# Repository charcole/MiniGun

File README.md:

# MiniGun - A mini super gun (JAMMA on TV)

A device for playing JAMMA compatible arcade boards on a TV using Wii Classic Controllers

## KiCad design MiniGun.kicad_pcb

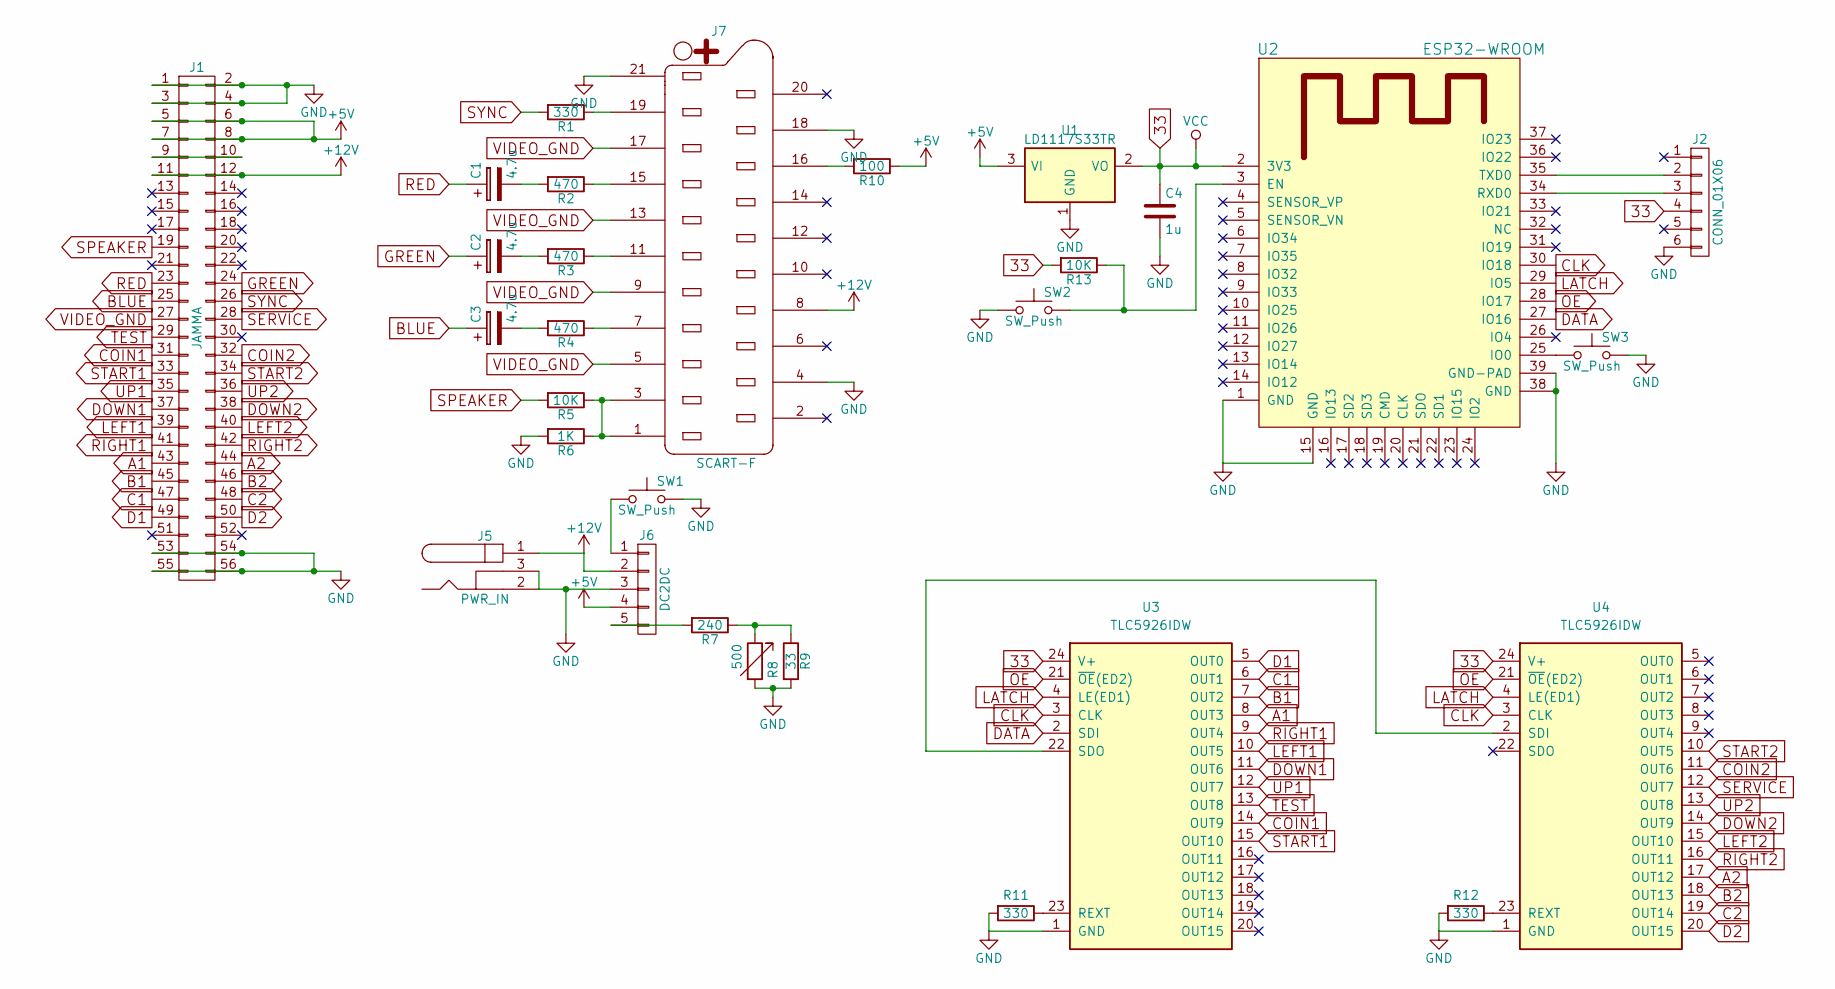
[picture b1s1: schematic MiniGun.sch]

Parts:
C1, C2, C3: 4.7u; C_1206_HandSoldering
C4: 1u; C_1206_HandSoldering
J1: JAMMA
J2: CONN_01X06; Pin_Header_Straight_1x06
J5: PWR_IN; BARREL_JACK
J6: DC2DC; NQR010A0X4Z
J7: SCART-F; SCART
R1, R11, R12: 330; R_1206_HandSoldering
R2, R3, R4: 470; R_1206_HandSoldering
R5, R13: 10K; R_1206_HandSoldering
R6: 1K; R_1206_HandSoldering
R7: 240; R_1206_HandSoldering
R8: 500; Potentiometer_Bourns_3296W_3-8Zoll_Inline_ScrewUp
R9: 33; R_1206_HandSoldering
R10: 100; R_1206_HandSoldering
SW1, SW2, SW3: SW_Push; SW_SPST_EVQPE1
U1: LD1117S33TR; SOT-223
U2: ESP32-WROOM
U3, U4: TLC5926IDW; SOIC-24W_7.5x15.4mm_Pitch1.27mm; MPN TLC5926IDW

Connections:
33: C4.1, J2.4, R13.2, U1.2 (VO), U2.2 (3V3), U3.24 (V+), U4.24 (V+)
+5V: J1.5, J1.6, J1.7, J1.8, J6.4, R10.1, U1.3 (VI)
+12V: J1.11, J1.12, J5.1, J6.2, J7.8
A1: J1.43, U3.8 (OUT3)
A2: J1.44, U4.17 (OUT12)
B1: J1.45, U3.7 (OUT2)
B2: J1.46, U4.18 (OUT13)
BLUE: C3.1, J1.25
C1: J1.47, U3.6 (OUT1)
C2: J1.48, U4.19 (OUT14)
CLK: U2.30 (IO18), U3.3 (CLK), U4.3 (CLK)
COIN1: J1.31, U3.14 (OUT9)
COIN2: J1.32, U4.11 (OUT6)
D1: J1.49, U3.5 (OUT0)
D2: J1.50, U4.20 (OUT15)
DATA: U2.27 (IO16), U3.2 (SDI)
DOWN1: J1.37, U3.11 (OUT6)
DOWN2: J1.38, U4.14 (OUT9)
GND: C4.2, J1.1, J1.2, J1.3, J1.4, J1.53, J1.54, J1.55, J1.56, J2.6, J5.2, J5.3, J6.3, J7.4, J7.18, J7.21, R6.2, R8.2, R9.2, R11.2, R12.2, SW1.2, SW2.1, SW3.2, U1.1 (GND), U2.1 (GND), U2.15 (GND), U2.38 (GND), U2.39 (GND-PAD), U3.1 (GND), U4.1 (GND)
GREEN: C2.1, J1.24
LATCH: U2.29 (IO5), U3.4 (LE(ED1)), U4.4 (LE(ED1))
LEFT1: J1.39, U3.10 (OUT5)
LEFT2: J1.40, U4.15 (OUT10)
unnamed: C1.2, R2.2
unnamed: C2.2, R3.2
unnamed: C3.2, R4.2
unnamed: J1.9, J1.10
unnamed: J2.2, U2.35 (TXD0)
unnamed: J2.3, U2.34 (RXD0)
unnamed: J6.1, SW1.1
unnamed: J6.5, R7.2
unnamed: J7.1, J7.3, R5.1, R6.1
unnamed: J7.7, R4.1
unnamed: J7.11, R3.1
unnamed: J7.15, R2.1
unnamed: J7.16, R10.2
unnamed: J7.19, R1.1
unnamed: R7.1, R8.1, R9.1
unnamed: R11.1, U3.23 (REXT)
unnamed: R12.1, U4.23 (REXT)
unnamed: R13.1, SW2.2, U2.3 (EN)
unnamed: SW3.1, U2.25 (IO0)
unnamed: U3.22 (SDO), U4.2 (SDI)
OE: U2.28 (IO17), U3.21 (~OE~(ED2)), U4.21 (~OE~(ED2))
RED: C1.1, J1.23
RIGHT1: J1.41, U3.9 (OUT4)
RIGHT2: J1.42, U4.16 (OUT11)
SERVICE: J1.28, U4.12 (OUT7)
SPEAKER: J1.19, R5.2
START1: J1.33, U3.15 (OUT10)
START2: J1.34, U4.10 (OUT5)
SYNC: J1.26, R1.2
TEST: J1.29, U3.13 (OUT8)
UP1: J1.35, U3.12 (OUT7)
UP2: J1.36, U4.13 (OUT8)
VIDEO_GND: J1.27, J7.5, J7.9, J7.13, J7.17

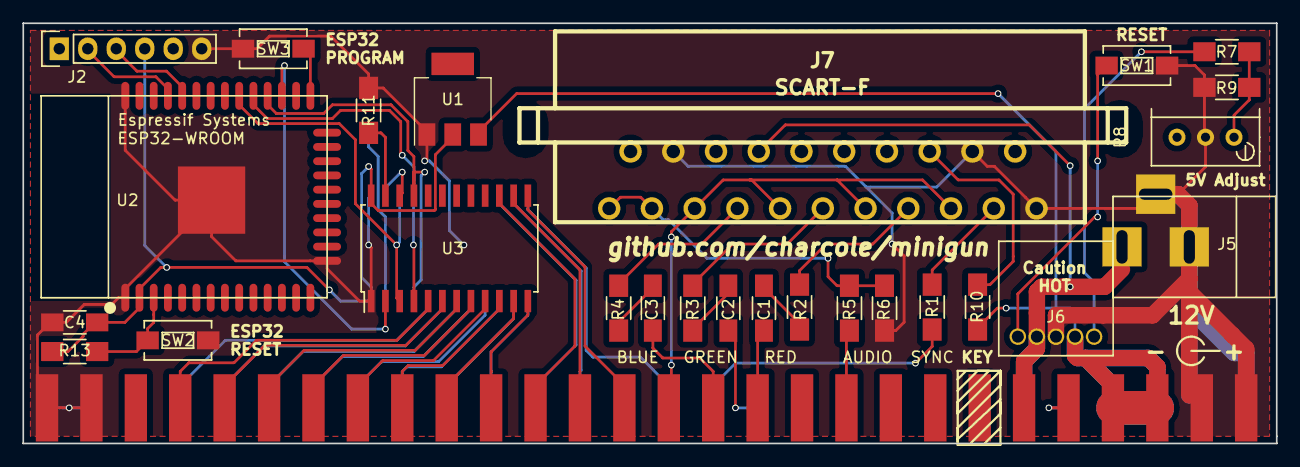
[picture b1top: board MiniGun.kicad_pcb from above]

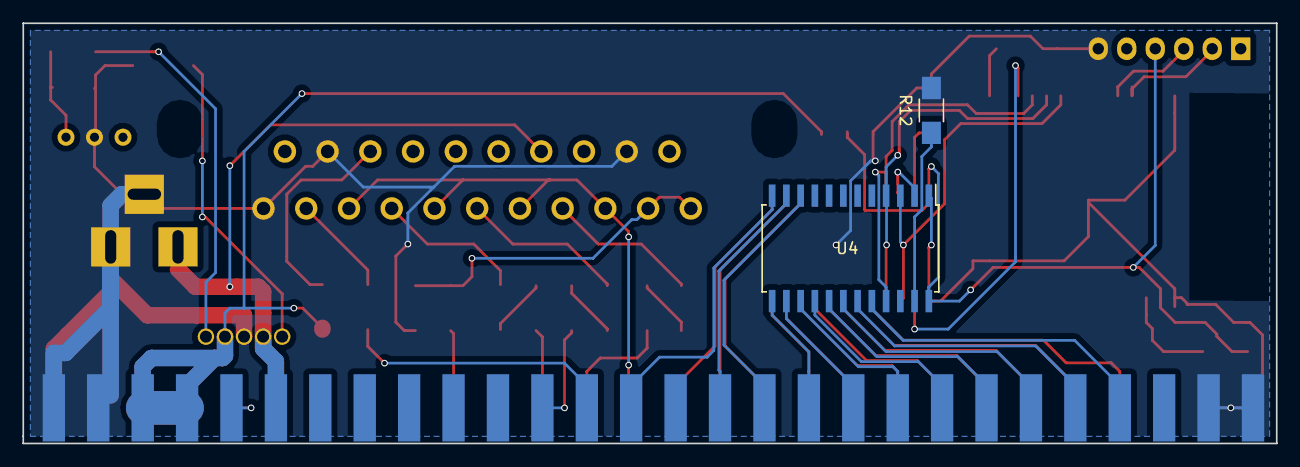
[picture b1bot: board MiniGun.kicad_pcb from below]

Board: 2 copper layers, 111.8 x 37.5 mm, 29 parts (2 on the bottom side), 56 nets.

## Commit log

2018-01-02 ESP32, shift register and buffer
2018-01-03 Changed over to NPN transistors as driver
2018-01-05 Simplied version using LED driver chips
2018-01-05 Removed backup files
2018-01-07 Added reset/upload buttons
2018-01-21 Removed an unused label
2018-01-21 Modified from LCDZapper, added support for Classic controller
2018-02-15 Renamed to MiniGun
2018-02-15 New picture
2018-02-15 Added license
2018-02-15 Added README
2018-02-15 Ignore build directory
2018-02-15 Added missing reset line pullup
